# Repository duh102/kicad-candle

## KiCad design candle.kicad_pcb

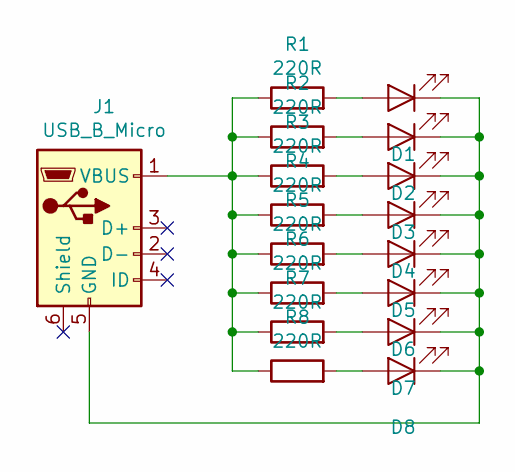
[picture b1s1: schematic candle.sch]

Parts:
D1, D2, D3, D4, D5, D6, D7, D8: LED; LED_D3.0mm
J1: USB_B_Micro; PinHeader_1x05_P2.54mm_Vertical
R1, R2, R3, R4, R5, R6, R7, R8: 220R; R_Axial_DIN0207_L6.3mm_D2.5mm_P7.62mm_Horizontal

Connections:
unnamed: D1.1 (K), D2.1 (K), D3.1 (K), D4.1 (K), D5.1 (K), D6.1 (K), D7.1 (K), D8.1 (K), J1.5 (GND)
unnamed: D1.2 (A), R1.2
unnamed: D2.2 (A), R2.2
unnamed: D3.2 (A), R3.2
unnamed: D4.2 (A), R4.2
unnamed: D5.2 (A), R5.2
unnamed: D6.2 (A), R6.2
unnamed: D7.2 (A), R7.2
unnamed: D8.2 (A), R8.2
unnamed: J1.1 (VBUS), R1.1, R2.1, R3.1, R4.1, R5.1, R6.1, R7.1, R8.1

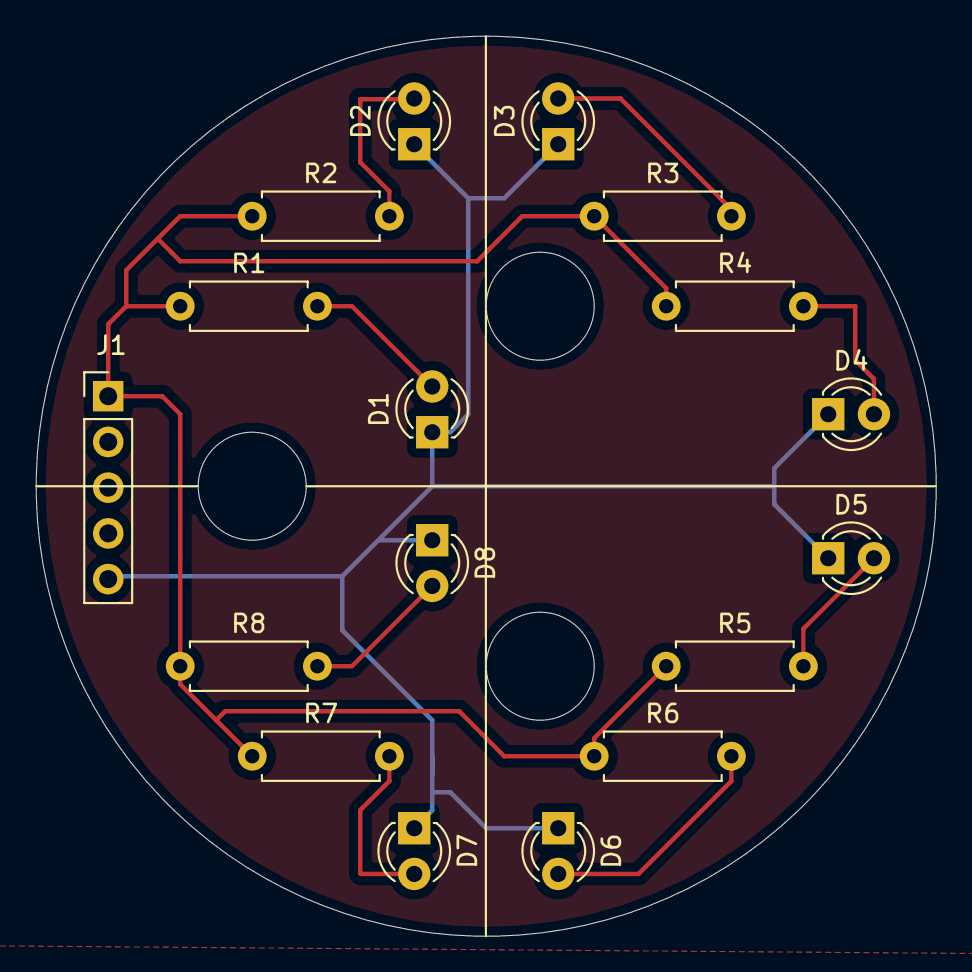
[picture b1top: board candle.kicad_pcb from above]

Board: 2 copper layers, 50.0 x 50.0 mm, 17 parts (0 on the bottom side), 10 nets.
